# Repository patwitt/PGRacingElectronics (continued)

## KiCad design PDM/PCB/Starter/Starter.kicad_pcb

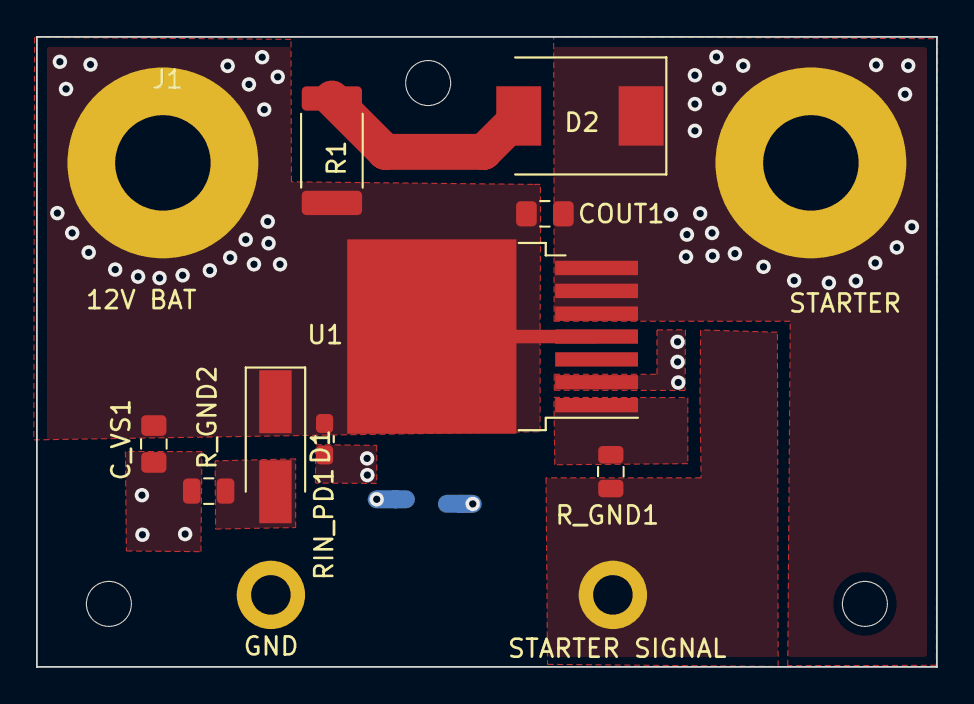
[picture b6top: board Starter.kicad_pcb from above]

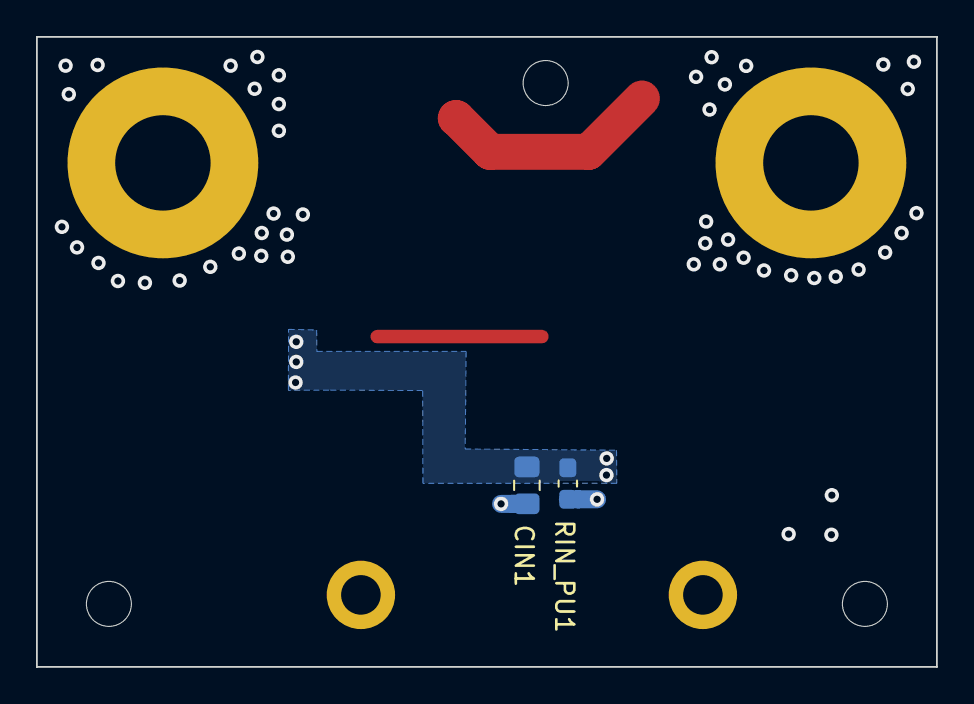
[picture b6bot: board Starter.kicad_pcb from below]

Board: 4 copper layers, 50.0 x 35.0 mm, 18 parts (2 on the bottom side), 8 nets.

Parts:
CIN1: 220nF; C_0805_2012Metric_Pad1.15x1.40mm_HandSolder
COUT1: 10nF; C_0805_2012Metric_Pad1.15x1.40mm_HandSolder
C_VS1: 100nF; C_0805_2012Metric_Pad1.15x1.40mm_HandSolder
D1: D_TVS_ALT; D_SMA_Handsoldering
D2: DIODE; D_SMC
GND: GND; MountingHole_2.2mm_M2_DIN965_Pad
H1, H3, H4: MountingHole; MountingHole_2.5mm
J1: 12V BAT; MountingHole_5.3mm_M5_Pad
J12: STARTER SIGNAL; MountingHole_2.2mm_M2_DIN965_Pad
R1: 0.22Ohm; R_2512_6332Metric
RIN_PD1: 22kR; R_0603_1608Metric_Pad1.05x0.95mm_HandSolder
RIN_PU1: 22k; R_0603_1608Metric_Pad1.05x0.95mm_HandSolder
R_GND1: 10R; R_0805_2012Metric
R_GND2: 1R; R_0805_2012Metric
STARTER: STARTER; MountingHole_5.3mm_M5_Pad
U1: BTS50010-1TAE; TO-263-7_TabPin4

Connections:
GND: CIN1.2, C_VS1.2, GND.1, RIN_PU1.1, R_GND2.1
unnamed: CIN1.1, RIN_PD1.2, RIN_PU1.2, U1.2
unnamed: COUT1.1, C_VS1.1, D1.1, J1.1, R1.2, RIN_PD1.1, U1.4
unnamed: COUT1.2, D2.1, STARTER.1, U1.5, U1.6, U1.7
unnamed: D1.2, R_GND2.2
unnamed: D2.2, R1.1
unnamed: J12.1, R_GND1.1
unnamed: R_GND1.2, U1.1

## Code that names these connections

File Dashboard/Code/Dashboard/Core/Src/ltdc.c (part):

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    __HAL_RCC_GPIOG_CLK_ENABLE();
    __HAL_RCC_GPIOD_CLK_ENABLE();
    /**LTDC GPIO Configuration
    PE4     ------> LTDC_B0
    PE5     ------> LTDC_G0
    PE6     ------> LTDC_G1
    PF10     ------> LTDC_DE
    PC0     ------> LTDC_R5
    PA1     ------> LTDC_R2
    PA2     ------> LTDC_R1
    PA3     ------> LTDC_B5
    PA4     ------> LTDC_VSYNC
    PA5     ------> LTDC_R4
    PA6     ------> LTDC_G2
    PB0     ------> LTDC_R3
    PB1     ------> LTDC_R6
    PB10     ------> LTDC_G4
    PB11     ------> LTDC_G5
    PG6     ------> LTDC_R7
    PG7     ------> LTDC_CLK
    PC6     ------> LTDC_HSYNC
    PC7     ------> LTDC_G6
    PA10     ------> LTDC_B1
    PD3     ------> LTDC_G7
    PD6     ------> LTDC_B2
    PG10     ------> LTDC_G3
    PG11     ------> LTDC_B3
    PG12     ------> LTDC_B4
    PG13     ------> LTDC_R0
    PB8     ------> LTDC_B6
    PB9     ------> LTDC_B7
    */
    GPIO_InitStruct.Pin = GPIO_PIN_4|GPIO_PIN_5|GPIO_PIN_6;
    GPIO_InitStruct.Mode = GPIO_MODE_AF_PP;
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    __HAL_RCC_LTDC_CLK_DISABLE();

    /**LTDC GPIO Configuration
    PE4     ------> LTDC_B0
    PE5     ------> LTDC_G0
    PE6     ------> LTDC_G1
    PF10     ------> LTDC_DE
    PC0     ------> LTDC_R5
    PA1     ------> LTDC_R2
    PA2     ------> LTDC_R1
    PA3     ------> LTDC_B5
    PA4     ------> LTDC_VSYNC
    PA5     ------> LTDC_R4
    PA6     ------> LTDC_G2
    PB0     ------> LTDC_R3
    PB1     ------> LTDC_R6
    PB10     ------> LTDC_G4
    PB11     ------> LTDC_G5
    PG6     ------> LTDC_R7
    PG7     ------> LTDC_CLK
    PC6     ------> LTDC_HSYNC
    PC7     ------> LTDC_G6
    PA10     ------> LTDC_B1
    PD3     ------> LTDC_G7
    PD6     ------> LTDC_B2
    PG10     ------> LTDC_G3
    PG11     ------> LTDC_B3
    PG12     ------> LTDC_B4
    PG13     ------> LTDC_R0
    PB8     ------> LTDC_B6
    PB9     ------> LTDC_B7
    */
    HAL_GPIO_DeInit(GPIOE, GPIO_PIN_4|GPIO_PIN_5|GPIO_PIN_6);

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
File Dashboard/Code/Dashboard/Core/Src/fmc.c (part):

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  __HAL_RCC_FMC_CLK_ENABLE();

  /** FMC GPIO Configuration
  PF0   ------> FMC_A0
  PF1   ------> FMC_A1
  PF2   ------> FMC_A2
  PF3   ------> FMC_A3
  PF4   ------> FMC_A4
  PF5   ------> FMC_A5
  PC2   ------> FMC_SDNE0
  PC3   ------> FMC_SDCKE0
  PA7   ------> FMC_SDNWE
  PF11   ------> FMC_SDNRAS
  PF12   ------> FMC_A6
  PF13   ------> FMC_A7
  PF14   ------> FMC_A8
  PF15   ------> FMC_A9
  PG0   ------> FMC_A10
  PE7   ------> FMC_D4
  PE8   ------> FMC_D5
  PE9   ------> FMC_D6
  PE10   ------> FMC_D7
  PE11   ------> FMC_D8
  PE12   ------> FMC_D9
  PE13   ------> FMC_D10
  PE14   ------> FMC_D11
  PE15   ------> FMC_D12
  PD8   ------> FMC_D13
  PD9   ------> FMC_D14
  PD10   ------> FMC_D15
  PD14   ------> FMC_D0
  PD15   ------> FMC_D1
  PG4   ------> FMC_BA0
  PG8   ------> FMC_SDCLK
  PD0   ------> FMC_D2
  PD1   ------> FMC_D3
  PG15   ------> FMC_SDNCAS
  PE0   ------> FMC_NBL0
  PE1   ------> FMC_NBL1
  */
  /* GPIO_InitStruct */
  GPIO_InitStruct.Pin = GPIO_PIN_0|GPIO_PIN_1|GPIO_PIN_2|GPIO_PIN_3
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  __HAL_RCC_FMC_CLK_DISABLE();

  /** FMC GPIO Configuration
  PF0   ------> FMC_A0
  PF1   ------> FMC_A1
  PF2   ------> FMC_A2
  PF3   ------> FMC_A3
  PF4   ------> FMC_A4
  PF5   ------> FMC_A5
  PC2   ------> FMC_SDNE0
  PC3   ------> FMC_SDCKE0
  PA7   ------> FMC_SDNWE
  PF11   ------> FMC_SDNRAS
  PF12   ------> FMC_A6
  PF13   ------> FMC_A7
  PF14   ------> FMC_A8
  PF15   ------> FMC_A9
  PG0   ------> FMC_A10
  PE7   ------> FMC_D4
  PE8   ------> FMC_D5
  PE9   ------> FMC_D6
  PE10   ------> FMC_D7
  PE11   ------> FMC_D8
  PE12   ------> FMC_D9
  PE13   ------> FMC_D10
  PE14   ------> FMC_D11
  PE15   ------> FMC_D12
  PD8   ------> FMC_D13
  PD9   ------> FMC_D14
  PD10   ------> FMC_D15
  PD14   ------> FMC_D0
  PD15   ------> FMC_D1
  PG4   ------> FMC_BA0
  PG8   ------> FMC_SDCLK
  PD0   ------> FMC_D2
  PD1   ------> FMC_D3
  PG15   ------> FMC_SDNCAS
  PE0   ------> FMC_NBL0
  PE1   ------> FMC_NBL1
  */

  HAL_GPIO_DeInit(GPIOF, GPIO_PIN_0|GPIO_PIN_1|GPIO_PIN_2|GPIO_PIN_3
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
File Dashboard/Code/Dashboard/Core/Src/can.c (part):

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
    __HAL_RCC_GPIOA_CLK_ENABLE();
    /**CAN1 GPIO Configuration
    PA11     ------> CAN1_RX
    PA12     ------> CAN1_TX
    */
    GPIO_InitStruct.Pin = GPIO_PIN_11|GPIO_PIN_12;
    GPIO_InitStruct.Mode = GPIO_MODE_AF_PP;
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
    __HAL_RCC_GPIOB_CLK_ENABLE();
    /**CAN2 GPIO Configuration
    PB12     ------> CAN2_RX
    PB13     ------> CAN2_TX
    */
    GPIO_InitStruct.Pin = GPIO_PIN_12|GPIO_PIN_13;
    GPIO_InitStruct.Mode = GPIO_MODE_AF_PP;
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    __HAL_RCC_CAN1_CLK_DISABLE();

    /**CAN1 GPIO Configuration
    PA11     ------> CAN1_RX
    PA12     ------> CAN1_TX
    */
    HAL_GPIO_DeInit(GPIOA, GPIO_PIN_11|GPIO_PIN_12);

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    }

    /**CAN2 GPIO Configuration
    PB12     ------> CAN2_RX
    PB13     ------> CAN2_TX
    */
    HAL_GPIO_DeInit(GPIOB, GPIO_PIN_12|GPIO_PIN_13);

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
